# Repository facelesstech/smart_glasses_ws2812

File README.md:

# smart_glasses_ws2812
smart_glasses_ws2812

Blog post - https://facelesstech.wordpress.com/2019/07/14/smart-glasses-ws2812-edition/
Youtube - https://youtu.be/2rOigdsKnWU

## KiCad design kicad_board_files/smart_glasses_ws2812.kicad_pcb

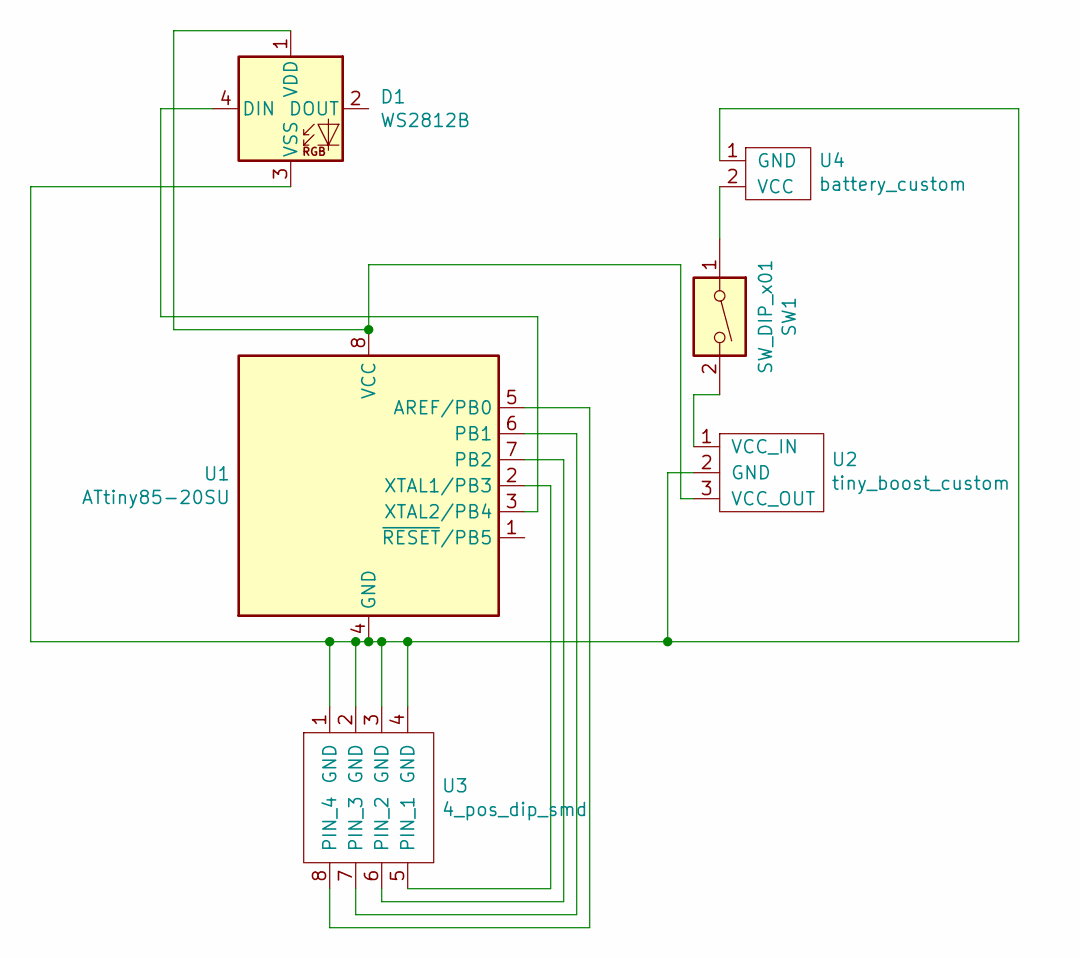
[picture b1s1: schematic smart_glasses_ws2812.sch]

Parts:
D1: WS2812B; ws2812_header_custom
SW1: SW_DIP_x01; tiny_smd_slide_switch_custom
U1: ATtiny85-20SU; SOIJ-8_5.3x5.3mm_P1.27mm
U2: tiny_boost_custom; Tiny_boost_custom
U3: 4_pos_dip_smd
U4: battery_custom; battery_connector_custom

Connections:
unnamed: D1.1 (VDD), U1.8 (VCC), U2.3 (VCC_OUT)
unnamed: D1.3 (VSS), U1.4 (GND), U2.2 (GND), U3.1 (GND), U3.2 (GND), U3.3 (GND), U3.4 (GND), U4.1 (GND)
unnamed: D1.4 (DIN), U1.3 (XTAL2/PB4)
unnamed: SW1.1, U4.2 (VCC)
unnamed: SW1.2, U2.1 (VCC_IN)
unnamed: U1.2 (XTAL1/PB3), U3.5 (PIN_1)
unnamed: U1.5 (AREF/PB0), U3.8 (PIN_4)
unnamed: U1.6 (PB1), U3.7 (PIN_3)
unnamed: U1.7 (PB2), U3.6 (PIN_2)

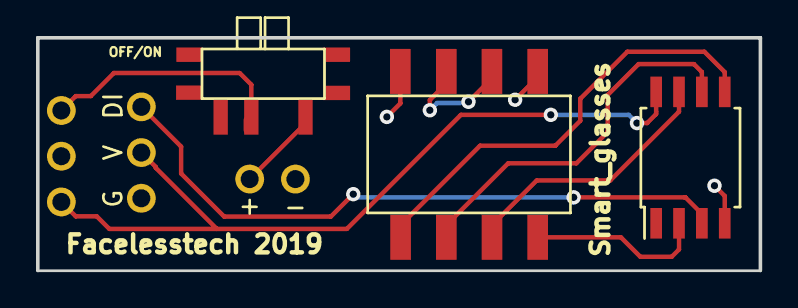
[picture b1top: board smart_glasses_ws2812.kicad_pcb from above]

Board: 2 copper layers, 40.1 x 12.9 mm, 6 parts (1 on the bottom side), 9 nets.

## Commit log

2019-07-14 board files
2019-07-14 first upload of code
2020-02-27 added links to readme
